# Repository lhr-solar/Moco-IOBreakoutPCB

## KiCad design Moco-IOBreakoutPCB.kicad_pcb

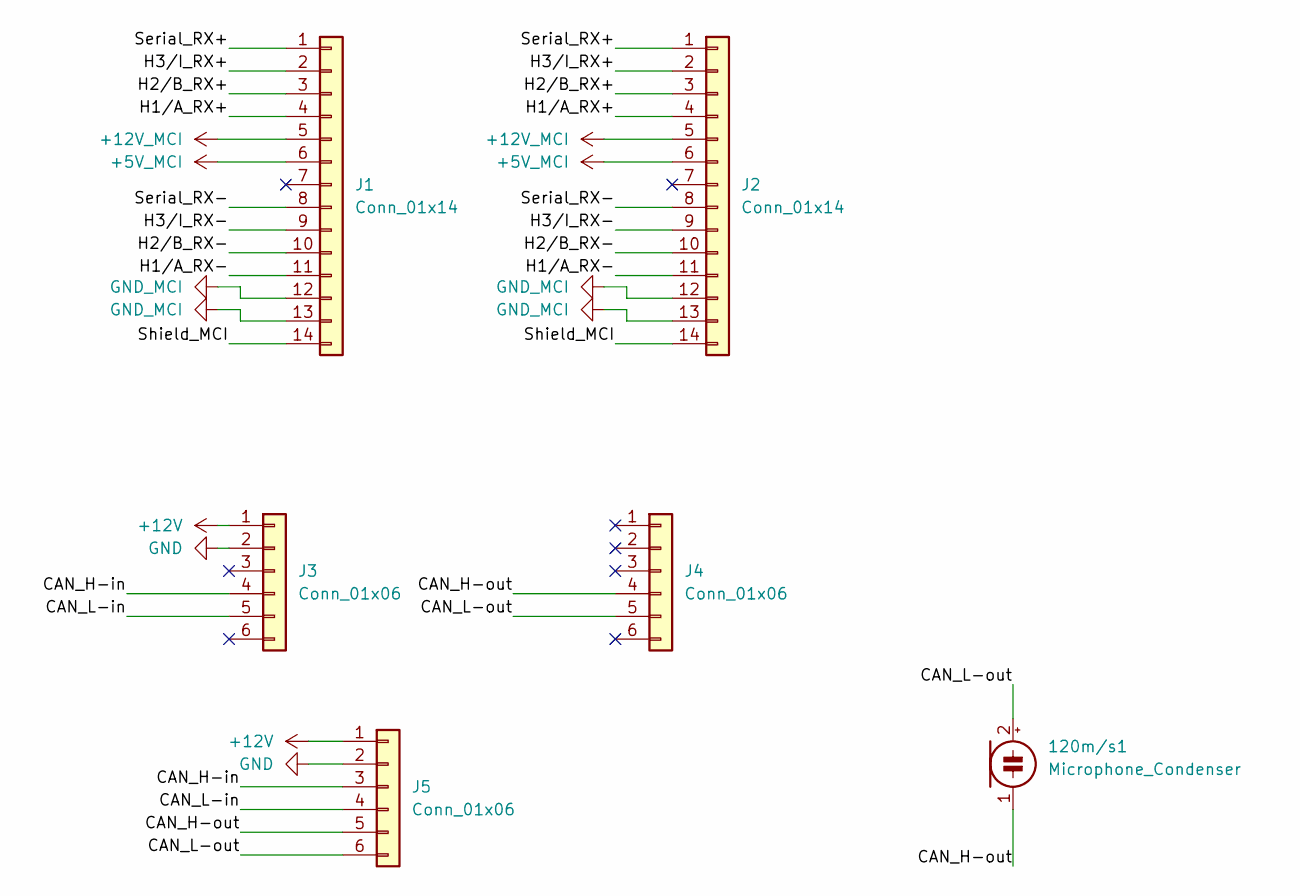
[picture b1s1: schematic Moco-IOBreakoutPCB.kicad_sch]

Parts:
120m/s1: Microphone_Condenser; R_0603_1608Metric
J1, J2: Conn_01x14; Molex_Microfit3.0_02x07_14-Pin-Vertical-PCB-Receptacle_4476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
J3, J4, J5: Conn_01x06; Molex_Microfit3.0_02x03_6-Pin-Vertical-PCB-Receptacle_44769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

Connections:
+5V_MCI: J1.6, J2.6
+12V: J3.1, J5.1
+12V_MCI: J1.5, J2.5
/CAN_H-in: J3.4, J5.3
/CAN_H-out: 120m/s1.1 (-), J4.4, J5.5
/CAN_L-in: J3.5, J5.4
/CAN_L-out: 120m/s1.2 (+), J4.5, J5.6
/H1/A_RX+: J1.4, J2.4
/H1/A_RX-: J1.11, J2.11
/H2/B_RX+: J1.3, J2.3
/H2/B_RX-: J1.10, J2.10
/H3/I_RX+: J1.2, J2.2
/H3/I_RX-: J1.9, J2.9
/Serial_RX+: J1.1, J2.1
/Serial_RX-: J1.8, J2.8
/Shield_MCI: J1.14, J2.14
GND: J3.2, J5.2
GND_MCI: J1.12, J1.13, J2.12, J2.13

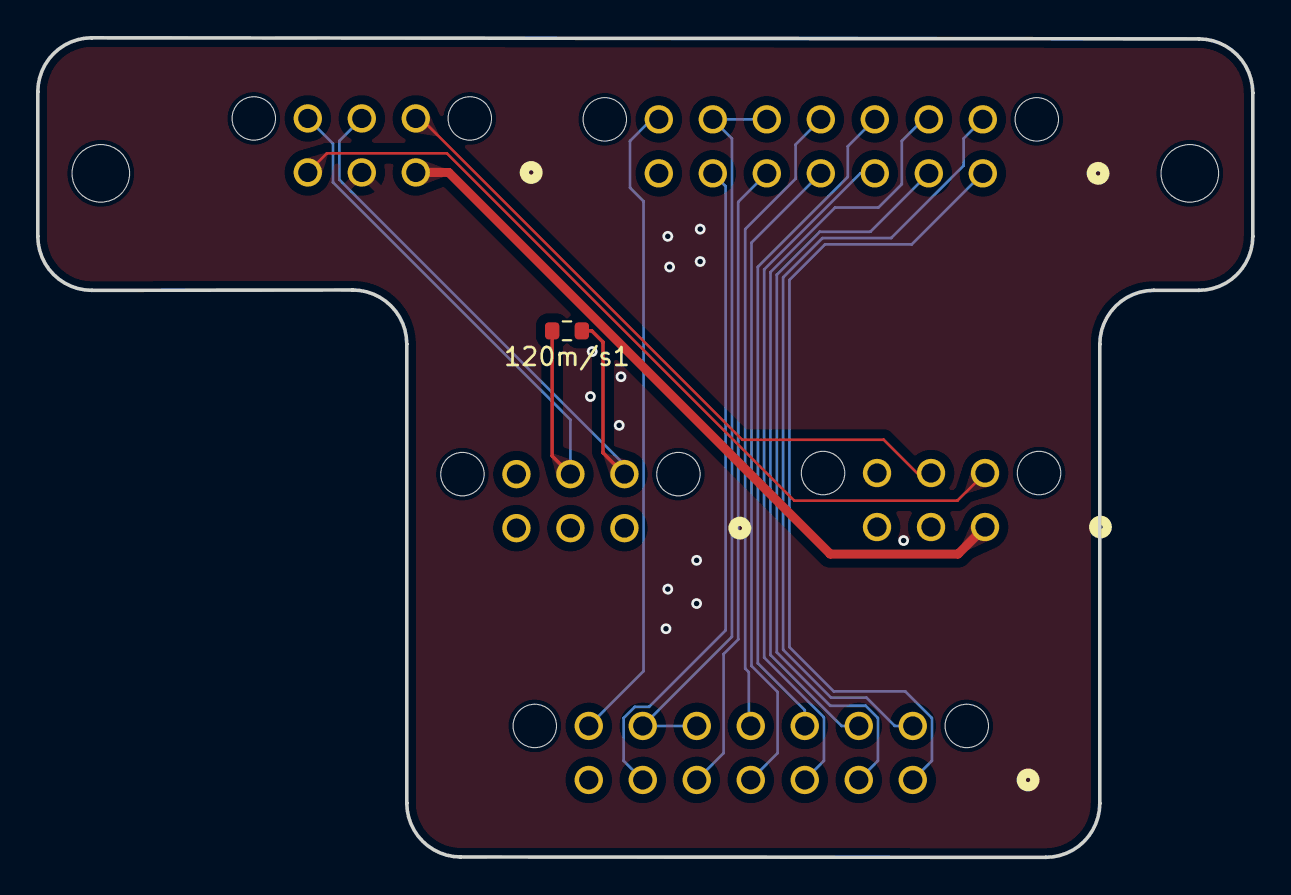
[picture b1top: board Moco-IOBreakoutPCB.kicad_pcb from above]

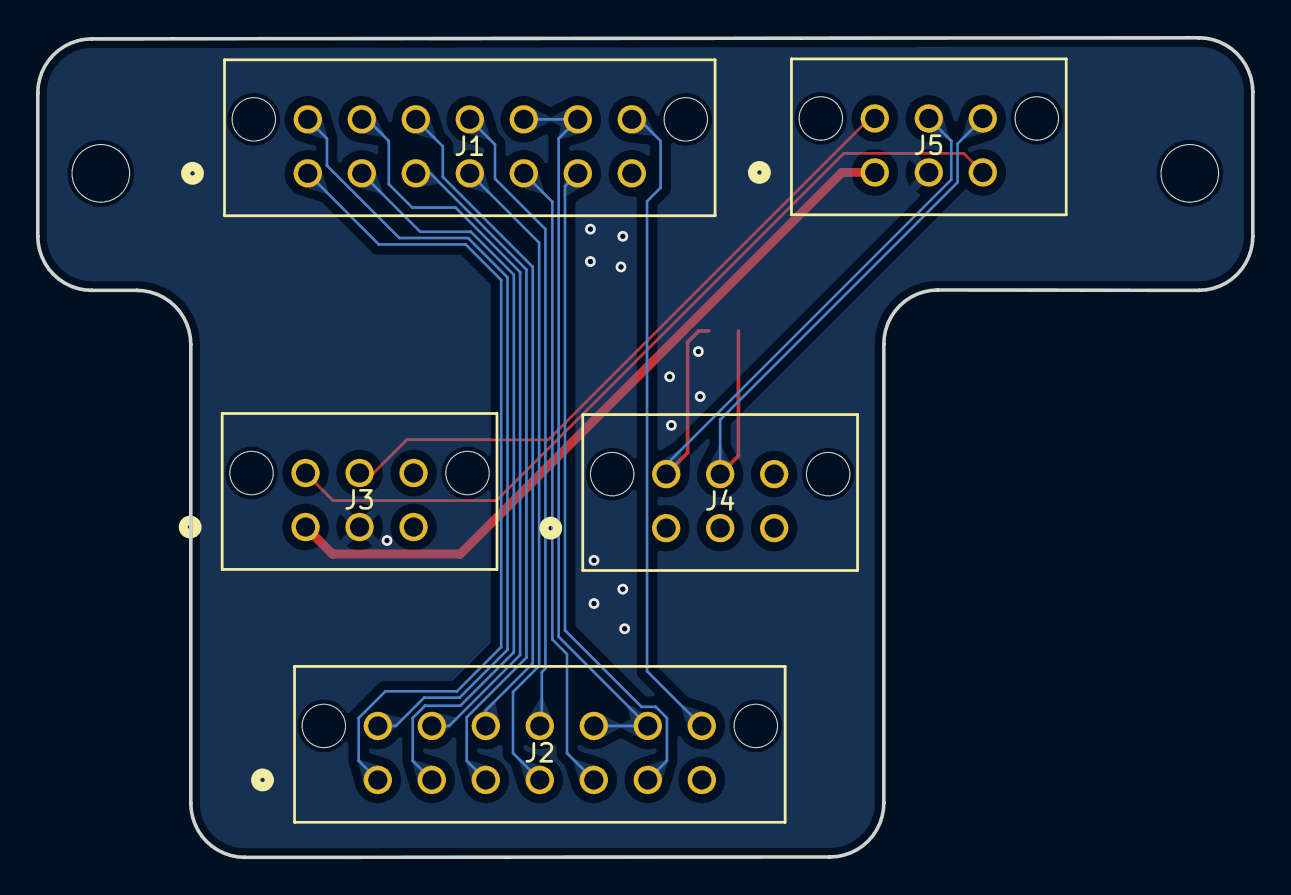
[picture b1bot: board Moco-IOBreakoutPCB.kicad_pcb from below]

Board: 2 copper layers, 67.5 x 45.5 mm, 6 parts (5 on the bottom side), 18 nets.

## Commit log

2025-08-20 layout
2025-08-20 final layout, no traces
2025-08-20 xt30 edit (not relevant)
2025-08-26 ravi do the traces
2025-09-09 routing
2025-09-29 120 ohm terminating microphone condenser
2025-10-12 type shi
